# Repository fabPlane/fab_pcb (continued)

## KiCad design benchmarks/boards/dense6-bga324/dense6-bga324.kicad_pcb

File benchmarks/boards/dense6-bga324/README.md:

# dense6-bga324 — dense 6-layer BGA/QFN fanout stress board

A synthetic, deterministic **candidate** board for stressing autorouters well beyond the frozen 26-case suite in
`benchmarks/autorouter/` (which it does not modify). It is not part of the scored suite; see
[Promotion gate](#promotion-gate) below.

| Property                  | Value                                                                                                                                                                                                  |
| ------------------------- | ------------------------------------------------------------------------------------------------------------------------------------------------------------------------------------------------------ |
| Outline                   | 70 x 56 mm rectangle                                                                                                                                                                                   |
| Copper                    | 6 layers (F.Cu, In1-In4, B.Cu), all signal; no planes — power/ground are routed as nets                                                                                                                |
| Connections               | **439** (263 nets: 260 two-pin signals + GND 102 pins, VCCIO 54 pins, VCC_CORE 26 pins)                                                                                                                |
| Pads / footprints         | 702 / 30                                                                                                                                                                                               |
| Parts                     | U1 324-ball BGA, 0.8 mm pitch (18x18, power in the centre 8x8); U2 96-ball memory BGA, 0.8 mm; U3 QFN-64 0.5 mm; U4 QFN-48 0.4 mm; J1/J2 2x30 0.5 mm board-to-board; 24x 0402 decoupling on the bottom |
| Rules                     | 0.1 mm track, 0.1 mm clearance, through via 0.45/0.2 mm, copper-to-edge 0.3 mm — **stored in `.kicad_pro`**                                                                                            |
| Native DRC (KiCad 10.0.6) | 0 errors, 439 unconnected, 30 `lib_footprint_issues` warnings (generated footprints have no library)                                                                                                   |

Signal nets are assigned to BGA balls by direction toward their destination, with a bounded local shuffle
(windows of 4) so that pin order is realistic but imperfect and some crossings are needed. The difficulty is
concentrated under and around U1 (minimum pad-to-edge distance is 3.8 mm, so the perimeter is mostly free); this is a
fanout/escape stress board rather than a uniformly dense one.

## Read this before using the board elsewhere

- **The rules live in the `.kicad_pro`, not in the `.kicad_pcb`.** Open or convert `dense6-bga324.kicad_pcb` together
  with `dense6-bga324.kicad_pro` (or use `case/board.*`). Opened on its own, KiCad falls back to its defaults
  (0.2 mm track / 0.2 mm clearance), which is a materially different (easier) problem. The `.dsn` carries the
  0.1/0.1 mm rules and the 0.45/0.2 mm via.
- **Footprints are pads only** (no courtyard, silkscreen or fabrication outlines). "0 DRC errors" therefore means no
  copper/clearance/edge errors on the unrouted board; courtyard overlap is not checked (`missing_courtyard` is an
  ignored check).

## Analytical margins (why it is hard)

| Constraint                                            | Available     | Needed                     | Spare                                                |
| ----------------------------------------------------- | ------------- | -------------------------- | ---------------------------------------------------- |
| Channel between adjacent 0.45 mm vias at 0.8 mm pitch | 0.35 mm       | 0.30 mm (one 0.1 mm track) | 50 µm                                                |
| Dog-bone via centre to ball centre (diagonal)         | 0.566 mm      | 0.525 mm                   | 41 µm                                                |
| Per-pin vias at the 0.4 mm QFN-48                     | 0.40 mm pitch | 0.55 mm                    | none — must stagger or escape on the top layer first |

Exactly one track fits per BGA channel, so escaping the outer rings of the 324-ball array on six layers is close to
the analytical limit.

## Promotion gate

Before this board is promoted into a scored suite (`role: "scored"`), record in this README a **best-known
solution**: a complete route that passes native KiCad DRC under these exact rules, produced by any reference engine
or by hand (at least one quadrant hand-routed if no engine completes it), with the tool/version and DRC report. Until
then a low completion rate cannot distinguish a weak router from an infeasible board.

Current best known result: fab_router `69cf598`, 101 / 439 connections, 0 new native DRC errors (1 seed). Not a
proof of routability.

## Files

- `dense6-bga324.kicad_pcb` / `.kicad_pro` — the board and its rules.
- `dense6-bga324.dsn` — Specctra DSN exported by KiCad 10.0.6 (`export_dsn.py`).
- `case/` — the same board in the `benchmarks/autorouter/cases/*` fixture layout (`board.*`, `baseline-drc.json`,
  `job.json` as job J1, `LICENSE`); `job.json` records the seed and the generator's sha256.
- `gen_dense6.py` (seed 6406), `make_case.py`, `export_dsn.py`, `project-template.kicad_pro` — generator, packaging
  scripts and the vendored KiCad project template.

## Regenerate

```
python3 gen_dense6.py /tmp/d6/gen --seed 6406
/usr/bin/python3 make_case.py /tmp/d6/gen/dense6-bga324.kicad_pcb /tmp/d6/out dense6-bga324 6406
```

Geometry, nets, rules and the DSN match the committed files. Expect `job.json` `utc` and the sha256 of
`board.kicad_pcb` / `baseline-drc.json` to differ (UUIDs KiCad assigns to default footprint fields when saving, and
the DRC report date). `job.json` uses `role: "tuning"` until the promotion gate above is met.

## Run it in the harness (private copy; the frozen suite stays untouched)

Copy `benchmarks/autorouter` elsewhere, copy `case/` to `cases/dense6-bga324-j1`, append a matching entry to that
copy's `suite.json` and update its `inputs.sha256.json` entry for `suite.json`, then
`python3 benchmark.py --smoke --case dense6-bga324-j1 --router fab-router --out results/dense6`.

Licence: MIT (see `LICENSE`), covering the generator, scripts and generated board files.

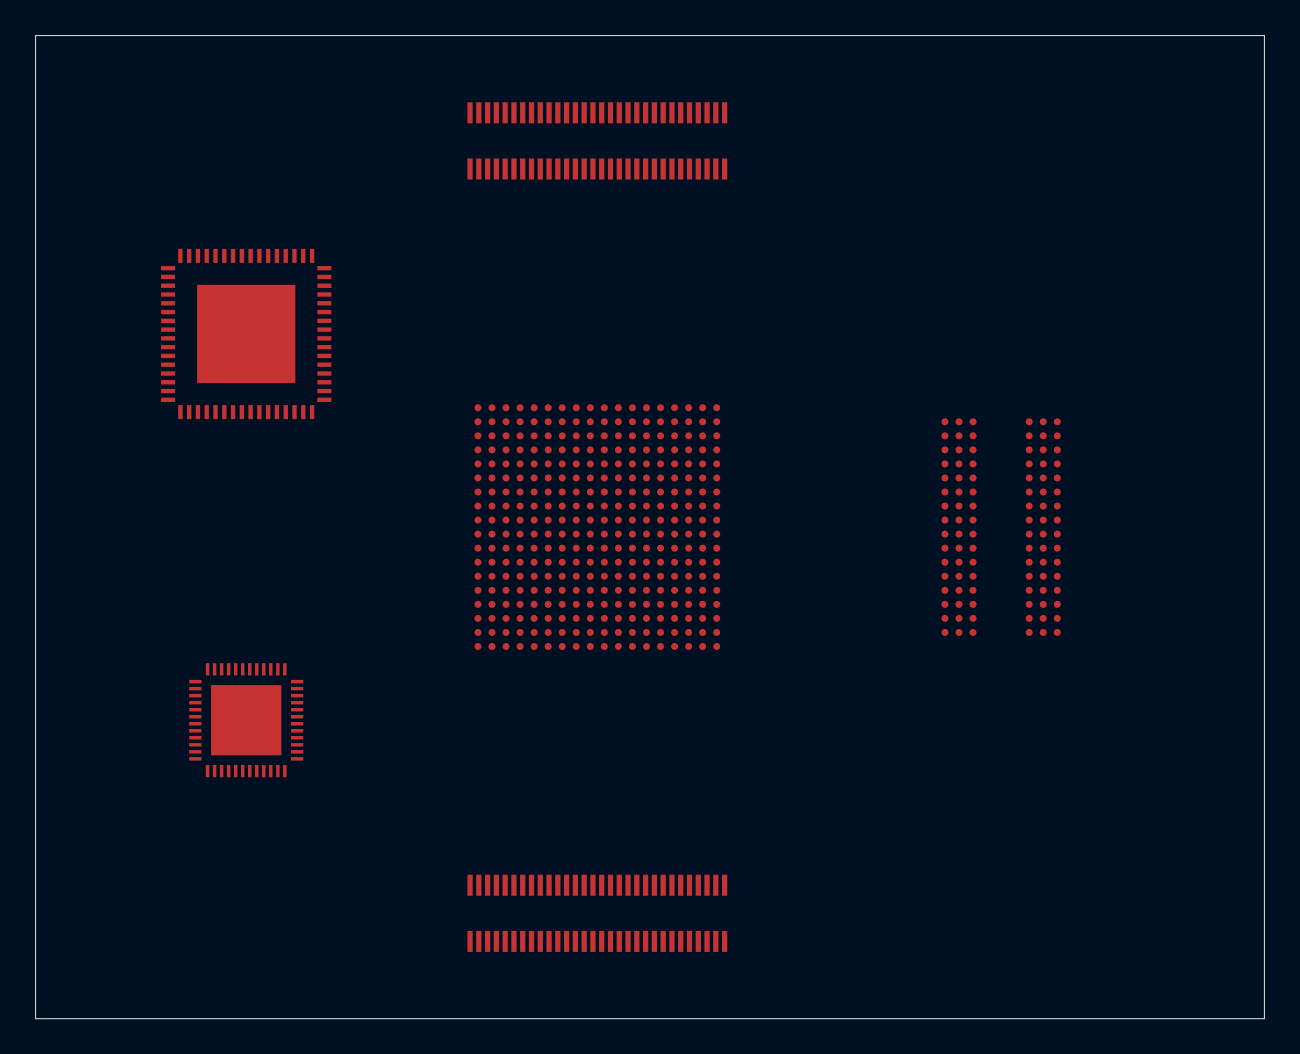
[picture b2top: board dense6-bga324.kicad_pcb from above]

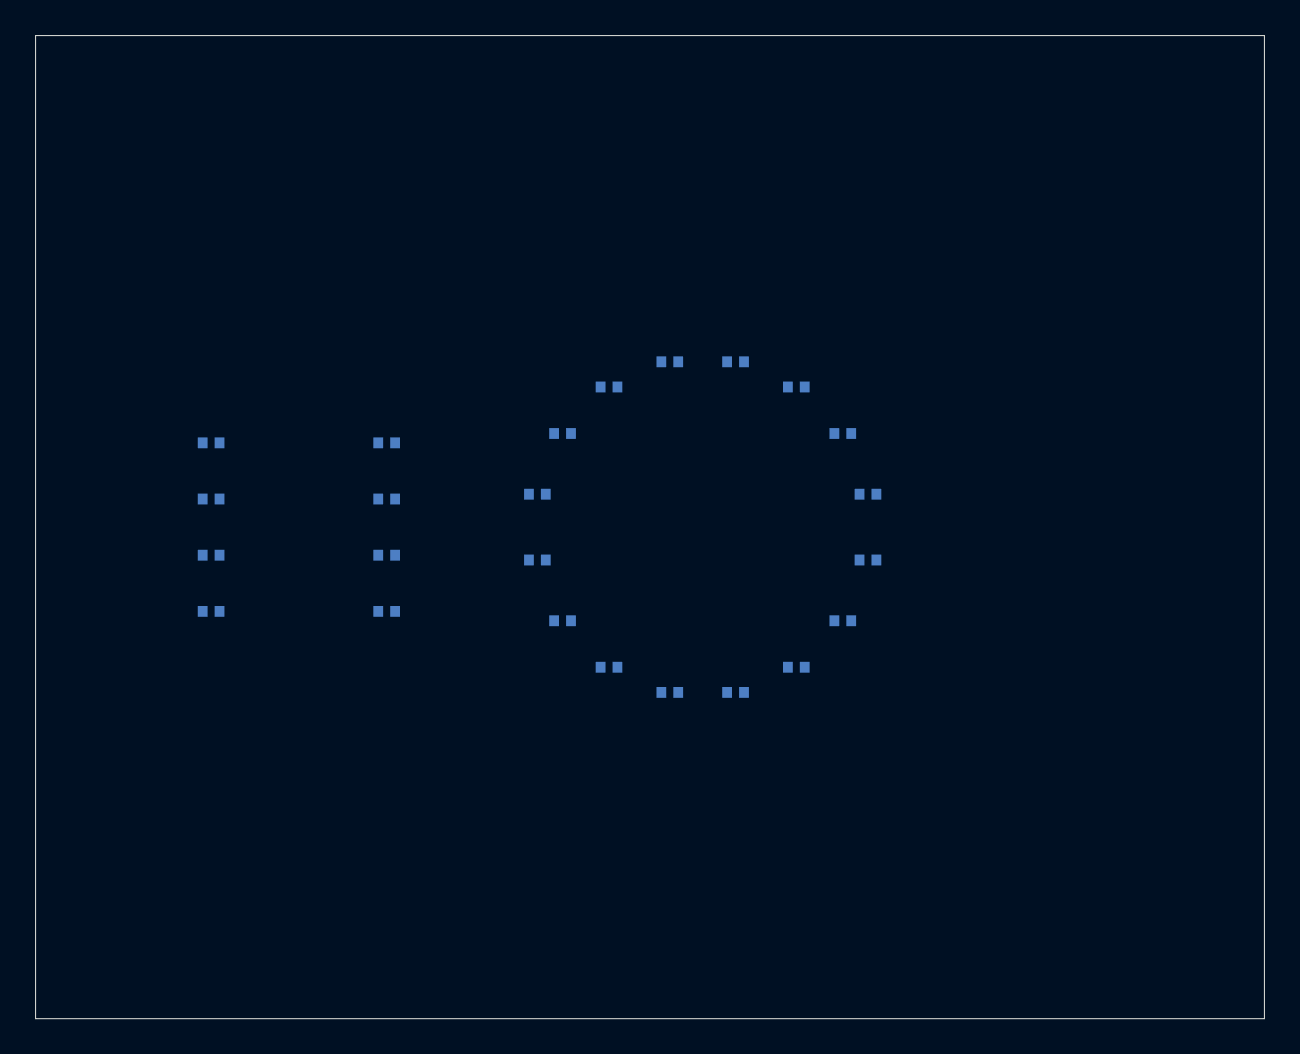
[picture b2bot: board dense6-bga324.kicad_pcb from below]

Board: 6 copper layers, 70.0 x 56.0 mm, 30 parts (24 on the bottom side), 263 nets, no tracks yet.

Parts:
C1, C2, C3, C4, C5, C6, C7, C8, C9, C10, C11, C12, C13, C14, C15, C16, C17, C18, C19, C20, C21, C22, C23, C24: 100nF_0402
J1, J2: B2B_2x30_0.5mm
U1: BGA324_0.8mm
U2: BGA96_0.8mm
U3: QFN64_0.5mm_9x9
U4: QFN48_0.4mm_6x6

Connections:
GND: C1.2, C2.2, C3.2, C4.2, C5.2, C6.2, C7.2, C8.2, C9.2, C10.2, C11.2, C12.2, C13.2, C14.2, C15.2, C16.2, C17.2, C18.2, C19.2, C20.2, C21.2, C22.2, C23.2, C24.2, J1.1, J1.2, J1.9, J1.10, J1.15, J1.16, J1.23, J1.24, J1.29, J1.30, J1.37, J1.38, J1.45, J1.46, J1.59, J1.60, J2.1, J2.2, J2.11, J2.12, J2.21, J2.22, J2.41, J2.42, J2.51, J2.52, J2.59, J2.60, U1.F6, U1.F8, U1.F10, U1.F12, U1.G7, U1.G9, U1.G11, U1.G13, U1.H6, U1.H8, U1.H10, U1.H12, U1.J7, U1.J9, U1.J11, U1.J13, U1.K6, U1.K8, U1.K10, U1.K12, U1.L7, U1.L9, U1.L11, U1.L13, U1.M6, U1.M8, U1.M10, U1.M12, U1.N7, U1.N9, U1.N11, U1.N13, U2.A3, U2.A4, U2.E3, U2.E4, U2.J3, U2.J4, U2.N3, U2.N4, U3.16, U3.32, U3.48, U3.64, U3.65, U4.12, U4.24, U4.36, U4.48, U4.49
JBOT_D0: J2.5, U1.T7
JBOT_D1: J2.6, U1.V6
JBOT_D2: J2.7, U1.V7
JBOT_D3: J2.8, U1.U7
JBOT_D4: J2.9, U1.T8
JBOT_D5: J2.10, U1.R8
JBOT_D6: J2.13, U1.U8
JBOT_D7: J2.14, U1.P8
JBOT_D8: J2.15, U1.P9
JBOT_D9: J2.16, U1.T9
JBOT_D10: J2.17, U1.V8
JBOT_D11: J2.18, U1.R9
JBOT_D12: J2.19, U1.P10
JBOT_D13: J2.20, U1.V9
JBOT_D14: J2.23, U1.U9
JBOT_D15: J2.24, U1.R10
JBOT_D16: J2.25, U1.U10
JBOT_D17: J2.26, U1.V10
JBOT_D18: J2.27, U1.T10
JBOT_D19: J2.28, U1.P11
JBOT_D20: J2.29, U1.R11
JBOT_D21: J2.30, U1.T11
JBOT_D22: J2.33, U1.V11
JBOT_D23: J2.34, U1.U11
JBOT_D24: J2.35, U1.U12
JBOT_D25: J2.36, U1.P12
JBOT_D26: J2.37, U1.T12
JBOT_D27: J2.38, U1.R12
JBOT_D28: J2.39, U1.R13
JBOT_D29: J2.40, U1.V12
JBOT_D30: J2.43, U1.T13
JBOT_D31: J2.44, U1.D13
JBOT_D32: J2.45, U1.C14
JBOT_D33: J2.46, U1.V13
JBOT_D34: J2.47, U1.U13
JBOT_D35: J2.48, U1.T14
JBOT_D36: J2.49, U1.B15
JBOT_D37: J2.50, U1.U14
JBOT_D38: J2.53, U1.V14
JBOT_D39: J2.54, U1.A15
JBOT_D40: J2.55, U1.V15
JBOT_D41: J2.56, U1.U15
JBOT_D42: J2.57, U1.V16
JBOT_D43: J2.58, U1.A16
JTOP_D0: J1.7, U1.A5
JTOP_D1: J1.8, U1.B6
JTOP_D2: J1.11, U1.A6
JTOP_D3: J1.12, U1.B5
JTOP_D4: J1.13, U1.C7
JTOP_D5: J1.14, U1.C6
JTOP_D6: J1.17, U1.A7
JTOP_D7: J1.18, U1.B7
JTOP_D8: J1.19, U1.A8
JTOP_D9: J1.20, U1.D7
JTOP_D10: J1.21, U1.E7
JTOP_D11: J1.22, U1.B8
JTOP_D12: J1.25, U1.E8
JTOP_D13: J1.26, U1.C8
JTOP_D14: J1.27, U1.D8
JTOP_D15: J1.28, U1.A9
JTOP_D16: J1.31, U1.C9
JTOP_D17: J1.32, U1.E9
JTOP_D18: J1.33, U1.B9
JTOP_D19: J1.34, U1.D9
JTOP_D20: J1.35, U1.B10
JTOP_D21: J1.36, U1.A10
JTOP_D22: J1.39, U1.D10
JTOP_D23: J1.40, U1.C10
JTOP_D24: J1.41, U1.C11
JTOP_D25: J1.42, U1.B11
JTOP_D26: J1.43, U1.E10
JTOP_D27: J1.44, U1.A11
JTOP_D28: J1.47, U1.E11
JTOP_D29: J1.48, U1.B12
JTOP_D30: J1.49, U1.A12
JTOP_D31: J1.50, U1.D11
JTOP_D32: J1.51, U1.C12
JTOP_D33: J1.52, U1.D12
JTOP_D34: J1.53, U1.A13
JTOP_D35: J1.54, U1.E12
JTOP_D36: J1.55, U1.B14
JTOP_D37: J1.56, U1.A14
JTOP_D38: J1.57, U1.B13
JTOP_D39: J1.58, U1.C13
MEM_D0: U1.A18, U2.A1
MEM_D1: U1.B17, U2.A2
MEM_D2: U1.A17, U2.A5
MEM_D3: U1.B16, U2.A6
MEM_D4: U1.B18, U2.B1
MEM_D5: U1.C16, U2.B2
MEM_D6: U1.C15, U2.B3
MEM_D7: U1.C17, U2.B4
MEM_D8: U1.D15, U2.B5
MEM_D9: U1.D14, U2.B6
MEM_D10: U1.C18, U2.C1
MEM_D11: U1.D16, U2.C2
MEM_D12: U1.D18, U2.C5
MEM_D13: U1.E14, U2.C6
MEM_D14: U1.D17, U2.D1
MEM_D15: U1.E13, U2.D2
MEM_D16: U1.E18, U2.D3
MEM_D17: U1.E15, U2.D4
MEM_D18: U1.E17, U2.D5
MEM_D19: U1.E16, U2.D6
MEM_D20: U1.F16, U2.E1
MEM_D21: U1.F15, U2.E2
MEM_D22: U1.F14, U2.E5
MEM_D23: U1.F17, U2.E6
MEM_D24: U1.G16, U2.F1
MEM_D25: U1.G15, U2.F2
MEM_D26: U1.G14, U2.F3
MEM_D27: U1.F18, U2.F4
MEM_D28: U1.G18, U2.F5
MEM_D29: U1.H14, U2.F6
MEM_D30: U1.G17, U2.G1
MEM_D31: U1.H15, U2.G2
MEM_D32: U1.H17, U2.G5
MEM_D33: U1.J14, U2.G6
MEM_D34: U1.H18, U2.H1
MEM_D35: U1.H16, U2.H2
MEM_D36: U1.J17, U2.H3
MEM_D37: U1.J18, U2.H4
MEM_D38: U1.J16, U2.H5
MEM_D39: U1.J15, U2.H6
MEM_D40: U1.K16, U2.J1
MEM_D41: U1.K14, U2.J2
MEM_D42: U1.K15, U2.J5
MEM_D43: U1.K17, U2.J6
MEM_D44: U1.L14, U2.K1
MEM_D45: U1.L16, U2.K2
MEM_D46: U1.L15, U2.K3
MEM_D47: U1.K18, U2.K4
MEM_D48: U1.M15, U2.K5
MEM_D49: U1.L18, U2.K6
MEM_D50: U1.M14, U2.L1
MEM_D51: U1.L17, U2.L2
MEM_D52: U1.M18, U2.L5
MEM_D53: U1.N14, U2.L6
MEM_D54: U1.M17, U2.M1
MEM_D55: U1.M16, U2.M2
MEM_D56: U1.N18, U2.M3
MEM_D57: U1.N15, U2.M4
MEM_D58: U1.N16, U2.M5
MEM_D59: U1.N17, U2.M6
MEM_D60: U1.P15, U2.N1
MEM_D61: U1.P16, U2.N2
MEM_D62: U1.P14, U2.N5
MEM_D63: U1.P13, U2.N6
MEM_D64: U1.P18, U2.P1
MEM_D65: U1.R15, U2.P2
MEM_D66: U1.R14, U2.P3
MEM_D67: U1.P17, U2.P4
MEM_D68: U1.R17, U2.P5
MEM_D69: U1.R16, U2.P6
MEM_D70: U1.T15, U2.R1
MEM_D71: U1.R18, U2.R2
MEM_D72: U1.T18, U2.R5
MEM_D73: U1.T17, U2.R6
MEM_D74: U1.U16, U2.T1
MEM_D75: U1.T16, U2.T2
MEM_D76: U1.V18, U2.T3
MEM_D77: U1.U17, U2.T4
MEM_D78: U1.U18, U2.T5
MEM_D79: U1.V17, U2.T6
QA_D0: U1.A3, U3.1
QA_D1: U1.A1, U3.2
QA_D2: U1.A2, U3.3
QA_D3: U1.A4, U3.4
QA_D4: U1.B1, U3.5
QA_D5: U1.B4, U3.6
QA_D6: U1.B2, U3.7
QA_D7: U1.B3, U3.9
QA_D8: U1.C5, U3.10
QA_D9: U1.C3, U3.11
QA_D10: U1.C4, U3.12
QA_D11: U1.C2, U3.13
QA_D12: U1.D5, U3.14
QA_D13: U1.D6, U3.15
QA_D14: U1.C1, U3.17
QA_D15: U1.D4, U3.18
QA_D16: U1.D2, U3.19
QA_D17: U1.E6, U3.20
QA_D18: U1.D3, U3.21
QA_D19: U1.D1, U3.22
QA_D20: U1.E2, U3.23
QA_D21: U1.E4, U3.25
QA_D22: U1.E5, U3.26
QA_D23: U1.E3, U3.27
QA_D24: U1.F4, U3.28
QA_D25: U1.F3, U3.29
QA_D26: U1.F5, U3.30
QA_D27: U1.E1, U3.31
QA_D28: U1.G5, U3.33
QA_D29: U1.G4, U3.34
QA_D30: U1.F1, U3.35
QA_D31: U1.F2, U3.36
QA_D32: U1.G1, U3.37
QA_D33: U1.G2, U3.38
QA_D34: U1.G3, U3.39
QA_D35: U1.H5, U3.41
QA_D36: U1.H4, U3.42
QA_D37: U1.H2, U3.43
QA_D38: U1.H3, U3.44
QA_D39: U1.H1, U3.45
QA_D40: U1.J4, U3.46
QA_D41: U1.J3, U3.47
QA_D42: U1.J2, U3.49
QA_D43: U1.J5, U3.50
QA_D44: U1.K5, U3.51
QA_D45: U1.J1, U3.52
QA_D46: U1.K4, U3.53
QA_D47: U1.K3, U3.54
QA_D48: U1.L3, U3.55
QA_D49: U1.K1, U3.57
QA_D50: U1.L4, U3.58
QA_D51: U1.K2, U3.59
QA_D52: U1.L1, U3.60
QA_D53: U1.M2, U3.61
QA_D54: U1.L2, U3.62
QA_D55: U1.M1, U3.63
QB_D0: U1.M5, U4.1
QB_D1: U1.L5, U4.2
QB_D2: U1.M4, U4.3
QB_D3: U1.M3, U4.4
QB_D4: U1.N4, U4.5
QB_D5: U1.N2, U4.7
QB_D6: U1.N3, U4.8
QB_D7: U1.N5, U4.9
QB_D8: U1.P6, U4.10
QB_D9: U1.N1, U4.11
QB_D10: U1.P7, U4.13
QB_D11: U1.P5, U4.14
QB_D12: U1.P4, U4.15
QB_D13: U1.P2, U4.16
QB_D14: U1.P1, U4.17
QB_D15: U1.P3, U4.19
QB_D16: U1.R6, U4.20
QB_D17: U1.R5, U4.21
QB_D18: U1.R7, U4.22
QB_D19: U1.R4, U4.23
QB_D20: U1.R3, U4.25
QB_D21: U1.T6, U4.26
QB_D22: U1.R1, U4.27
QB_D23: U1.R2, U4.28
QB_D24: U1.T3, U4.29
QB_D25: U1.T2, U4.31
QB_D26: U1.T5, U4.32
QB_D27: U1.T4, U4.33
QB_D28: U1.U6, U4.34
QB_D29: U1.U5, U4.35
QB_D30: U1.U4, U4.37
QB_D31: U1.T1, U4.38
QB_D32: U1.U2, U4.39
QB_D33: U1.U1, U4.40
QB_D34: U1.V5, U4.41
QB_D35: U1.U3, U4.43
QB_D36: U1.V4, U4.44
QB_D37: U1.V3, U4.45
QB_D38: U1.V1, U4.46
QB_D39: U1.V2, U4.47
VCCIO: C2.1, C4.1, C6.1, C8.1, C10.1, C12.1, C14.1, C16.1, C17.1, C18.1, C19.1, C20.1, C21.1, C22.1, C23.1, C24.1, J1.5, J1.6, J2.3, J2.4, J2.31, J2.32, U1.K7, U1.K9, U1.K11, U1.K13, U1.L6, U1.L8, U1.L10, U1.L12, U1.M7, U1.M9, U1.M11, U1.M13, U1.N6, U1.N8, U1.N10, U1.N12, U2.C3, U2.C4, U2.G3, U2.G4, U2.L3, U2.L4, U2.R3, U2.R4, U3.8, U3.24, U3.40, U3.56, U4.6, U4.18, U4.30, U4.42
VCC_CORE: C1.1, C3.1, C5.1, C7.1, C9.1, C11.1, C13.1, C15.1, J1.3, J1.4, U1.F7, U1.F9, U1.F11, U1.F13, U1.G6, U1.G8, U1.G10, U1.G12, U1.H7, U1.H9, U1.H11, U1.H13, U1.J6, U1.J8, U1.J10, U1.J12
